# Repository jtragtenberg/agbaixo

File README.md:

# Agbaixo
Instrumento Agbaixo, em processo de criação pelo BongarBit

# Para mandar o código para o Arduino:

Baixe e instale o Arduino na versão legado (1.8.x) em https://www.arduino.cc/en/software

Abra o programa Arduino (Arduino IDE)

Instale as bibliotecas colocando no diretório onde o Arduino for instalado, dentro da pasta libraries, todas as pastas que estão em Arduino/libraries deste repositório.

Na IDE do Arduino, vá nas configurações (File > Preferences) e adicione o texto na caixa de texto "Additional Board Manager URLs" o seguinte link: https://raw.githubusercontent.com/sparkfun/Arduino_Boards/main/IDE_Board_Manager/package_sparkfun_index.json

Vá em Tools>Board>Boards Manager e faça uma busca por Sparkfun AVR Boards e clique no botão "Install"

Vá em Tools>Board> e selecione a placa Arduino Pro Micro

Vá em Tools>Processor: e selecione o "ATmega 32u4 (5v, 16MHz)"

Identifique quais opções existem em Tools>Port>

Conecte o arduino no USB do computador

Note qual foi a opção nova que apareceu no submenu Tools>Port> e selecione ela

Abra o arquivo Arduino/agbaixo/agbaixo.ino e clique na barra de ferramentas da IDE do Arduino no botão "Upload" (o segundo da esquerda pra direita)

Se tudo der certo o código será enviado para a memória do Arduino.

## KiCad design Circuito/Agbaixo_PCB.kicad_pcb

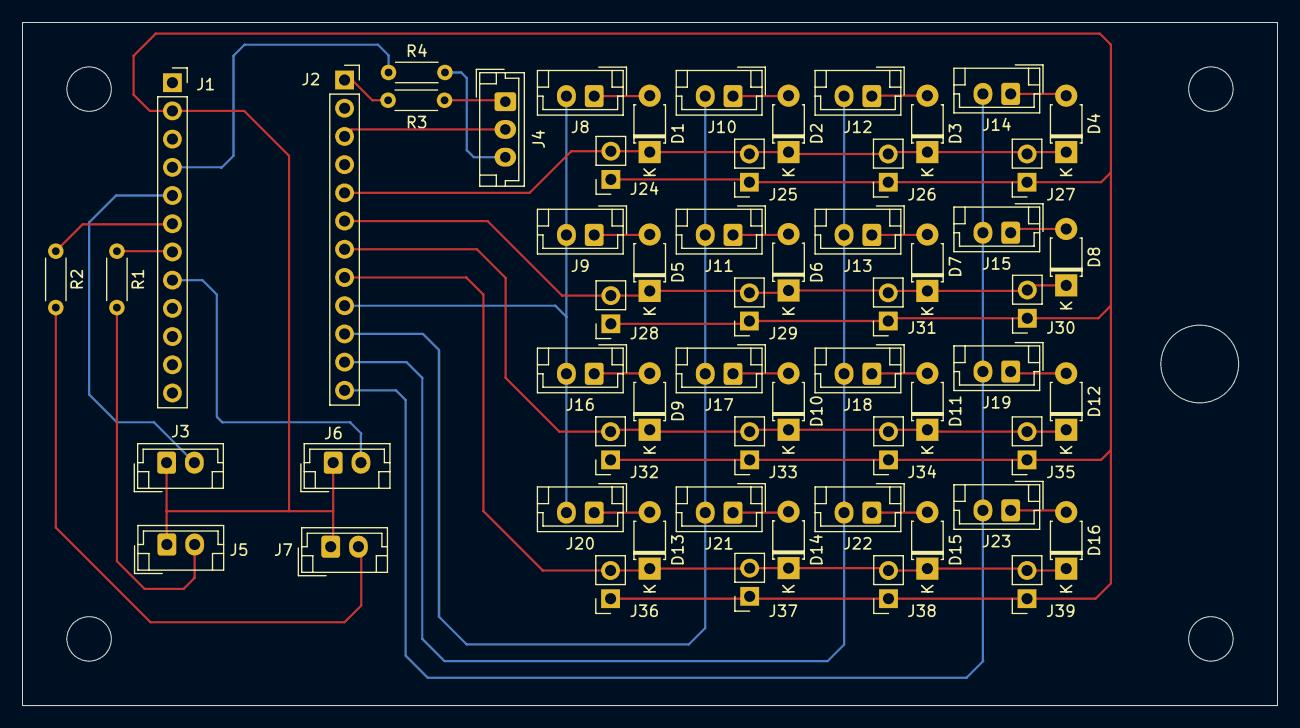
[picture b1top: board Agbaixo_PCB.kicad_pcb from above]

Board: 2 copper layers, 113.0 x 61.5 mm, 59 parts (0 on the bottom side), 36 nets.

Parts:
D1, D2, D3, D4, D5, D6, D7, D8, D9, D10, D11, D12, D13, D14, D15, D16: D; D_T-1_P5.08mm_Horizontal
J1, J2: Conn_01x12_Socket; PinSocket_1x12_P2.54mm_Vertical
J3, J5, J6, J7, J8, J9, J10, J11, J12, J13, J14, J15, J16, J17, J18, J19, J20, J21, J22, J23: Conn_01x02_Socket; JST_EH_B2B-EH-A_1x02_P2.50mm_Vertical
J4: Conn_01x03_Socket; JST_EH_B3B-EH-A_1x03_P2.50mm_Vertical
J24, J25, J26, J27, J28, J29, J30, J31, J32, J33, J34, J35, J36, J37, J38, J39: Conn_01x02_Pin; PinSocket_1x02_P2.54mm_Vertical
R1, R2, R3, R4: 220R; R_Axial_DIN0204_L3.6mm_D1.6mm_P5.08mm_Horizontal

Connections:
unnamed: D1.2 (A), J8.1
unnamed: D1.1 (K), D2.1 (K), D3.1 (K), D4.1 (K), J2.5, J24.2, J25.2, J26.2, J27.2
unnamed: D2.2 (A), J10.1
unnamed: D3.2 (A), J12.1
unnamed: D4.2 (A), J14.1
unnamed: D5.2 (A), J9.1
unnamed: D5.1 (K), D6.1 (K), D7.1 (K), D8.1 (K), J2.6, J28.2, J29.2, J30.2, J31.2
unnamed: D6.2 (A), J11.1
unnamed: D7.2 (A), J13.1
unnamed: D8.2 (A), J15.1
unnamed: D9.2 (A), J16.1
unnamed: D10.2 (A), J17.1
unnamed: D9.1 (K), D10.1 (K), D11.1 (K), D12.1 (K), J2.7, J32.2, J33.2, J34.2, J35.2
unnamed: D11.2 (A), J18.1
unnamed: D12.2 (A), J19.1
unnamed: D13.2 (A), J20.1
unnamed: D13.1 (K), D14.1 (K), D15.1 (K), D16.1 (K), J2.8, J36.2, J37.2, J38.2, J39.2
unnamed: D14.2 (A), J21.1
unnamed: D15.2 (A), J22.1
unnamed: D16.2 (A), J23.1
unnamed: J1.2, J3.1, J5.1, J6.1, J7.1, J24.1, J25.1, J26.1, J27.1, J28.1, J29.1, J30.1, J31.1, J32.1, J33.1, J34.1, J35.1, J36.1, J37.1, J38.1, J39.1
unnamed: J1.4, R4.1
unnamed: J1.5, J3.2
unnamed: J1.6, R2.1
unnamed: J1.7, R1.1
unnamed: J1.8, J6.2
unnamed: J2.1, R3.1
unnamed: J2.3, J4.2
unnamed: J4.1, R3.2
unnamed: J4.3, R4.2
unnamed: J5.2, R1.2
unnamed: J7.2, R2.2
unnamed: J2.10, J10.2, J11.2, J17.2, J21.2
unnamed: J2.11, J12.2, J13.2, J18.2, J22.2
unnamed: J2.12, J14.2, J15.2, J19.2, J23.2
unnamed: J2.9, J8.2, J9.2, J16.2, J20.2

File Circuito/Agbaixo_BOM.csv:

"Reference","Value","Datasheet","Footprint","Qty","DNP"
"D1,D2,D3,D4,D5,D6,D7,D8,D9,D10,D11,D12,D13,D14,D15,D16","D","~","Diode_THT:D_T-1_P5.08mm_Horizontal","16",""
"J1,J2","Conn_01x12_Socket","~","Connector_PinSocket_2.54mm:PinSocket_1x12_P2.54mm_Vertical","2",""
"J3,J5,J6,J7,J8,J9,J10,J11,J12,J13,J14,J15,J16,J17,J18,J19,J20,J21,J22,J23","Conn_01x02_Socket","~","Connector_JST:JST_EH_B2B-EH-A_1x02_P2.50mm_Vertical","20",""
"J4","Conn_01x03_Socket","~","Connector_JST:JST_EH_B3B-EH-A_1x03_P2.50mm_Vertical","1",""
"J24,J25,J26,J27,J28,J29,J30,J31,J32,J33,J34,J35,J36,J37,J38,J39","Conn_01x02_Pin","~","Connector_PinSocket_2.54mm:PinSocket_1x02_P2.54mm_Vertical","16",""
"R1,R2,R3,R4","220R","~","Resistor_THT:R_Axial_DIN0204_L3.6mm_D1.6mm_P5.08mm_Horizontal","4",""

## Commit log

2024-01-03 commit inicial
2024-01-03 Velocity nos Botoes
2024-01-03 modo repeat
2024-01-03 2 modos: modo repeat e modo botoes
2024-01-03 correcao no readme
2024-01-03 adicionei as bibliotecas usadas
2024-01-03 tutorial no readme
2024-01-03 gitignore
2024-01-26 adaptei o codigo arduino pra botoes novos
2024-12-10 changed gitignore and filenames
2025-05-21 Added sampler from other repo to this
2025-05-21 added Bela Sampelr
2025-05-21 organized all
2025-05-21 renamed folder
2025-05-21 added video to README.md
2026-03-24 Remove Bela sampler project directories
